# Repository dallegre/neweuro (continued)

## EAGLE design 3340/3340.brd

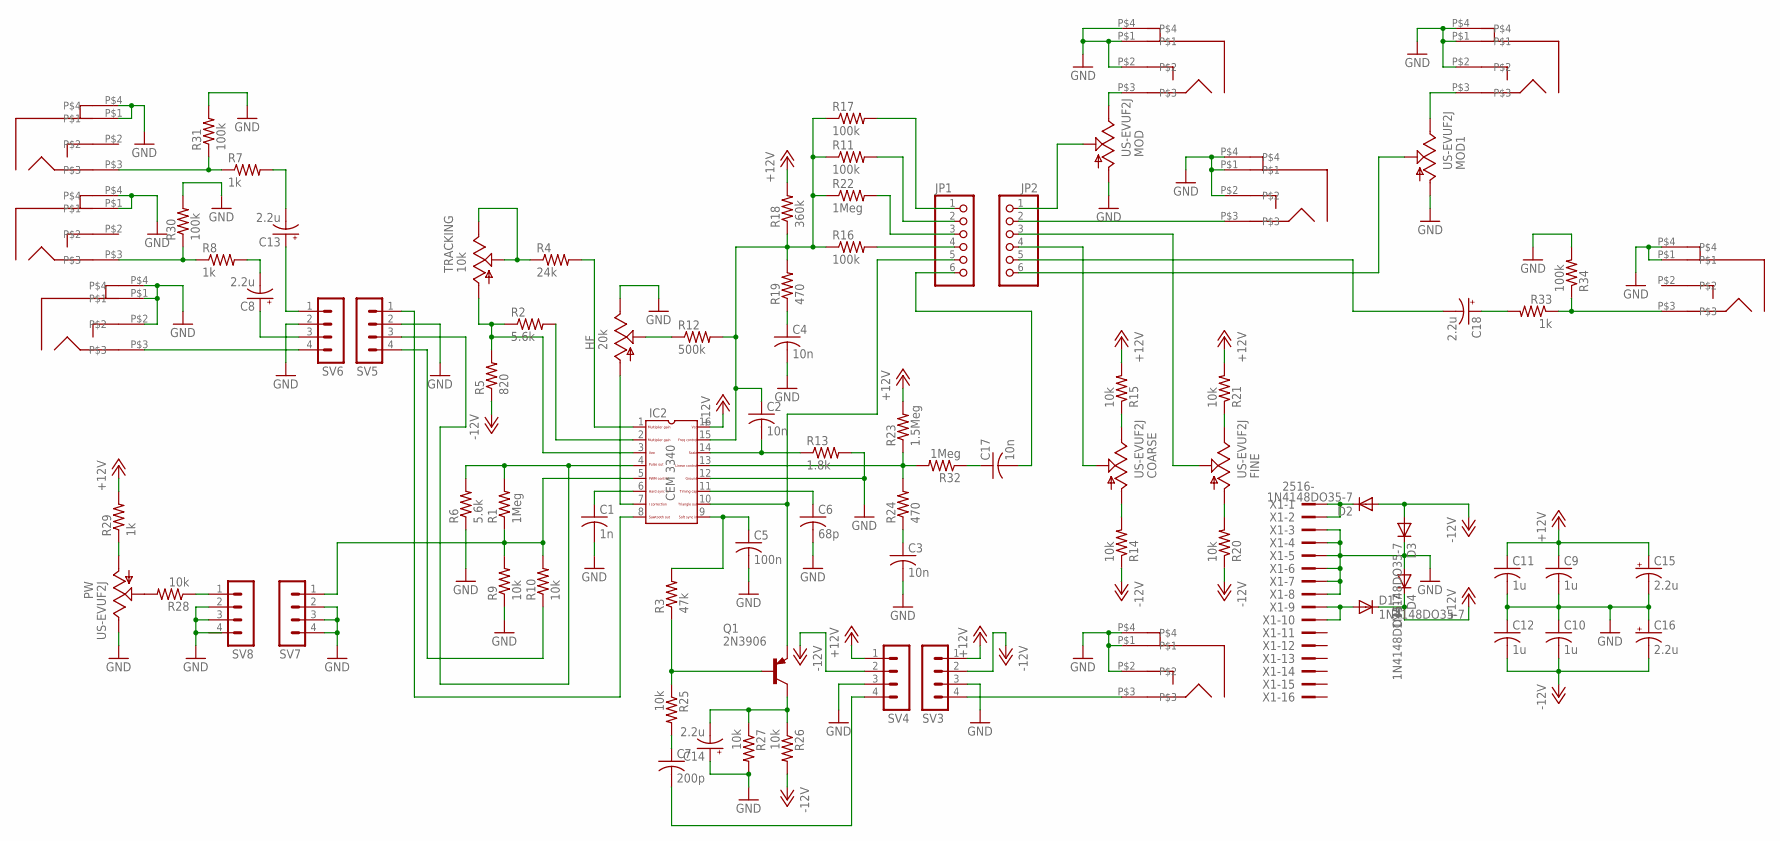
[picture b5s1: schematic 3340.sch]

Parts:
C1: 1n; C050-025X075
C2, C3, C4, C17: 10n; C050-025X075
C5: 100n; C050-025X075
C6: 68p; C050-025X075
C7: 200p; C050-025X075
C8, C13, C14, C15, C16, C18: 2.2u; E2,5-6
C9, C10, C11, C12: 1u; C050-025X075
COARSE: US-EVUF2J; EVUFXJ
CVIN1, CVIN2: PJ301BM
D1, D2, D3, D4: 1N4148DO35-7; DO35-7
EXPMOD: PJ301BM
FINE: US-EVUF2J; EVUFXJ
HF: 20k; S64W
IC2: CEM3340; DIL16
JP1, JP2: PINHD-1X6; 1X06
MOD, MOD1: US-EVUF2J; EVUFXJ
PULSE: PJ301BM
PW: US-EVUF2J; EVUFXJ
PWM: PJ301BM
Q1: 2N3906; TO92
R1, R22, R32: 1Meg; 0207/2V
R2, R6: 5.6k; 0207/2V
R3: 47k; 0207/2V
R4: 24k; 0207/2V
R5: 820; 0207/2V
R7, R8, R29, R33: 1k; 0207/7
R9, R10, R25, R26, R27: 10k; 0207/2V
R11, R16, R17: 100k; 0207/2V
R12: 500k; 0207/2V
R13: 1.8k; 0207/2V
R14, R15, R20, R21, R28: 10k; 0207/7
R18: 360k; 0207/2V
R19, R24: 470; 0207/2V
R23: 1.5Meg; 0207/2V
R30, R31, R34: 100k; 0207/7
SAW, SAW1: PJ301BM
SV3, SV4, SV5, SV6, SV7, SV8: MA04-1
SYNC: PJ301BM
TRACKING: 10k; S64W
X1: 2516-; PAK100/2500-16

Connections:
+12V: C9.1, C11.1, C15.+, D1.C, D4.C, IC2.16, R15.2, R18.2, R21.2, R23.2, R29.2, SV3.1, SV4.1
-12V: C10.2, C12.2, C16.-, D2.A, D3.A, R5.1, R14.1, R20.1, R26.2, SV3.2, SV4.2
GND: C1.2, C3.2, C4.2, C5.2, C6.2, C9.2, C10.1, C11.2, C12.1, C14.+, C15.-, C16.+, CVIN1.P$1, CVIN1.P$2, CVIN1.P$4, CVIN2.P$1, CVIN2.P$2, CVIN2.P$4, D3.C, D4.A, EXPMOD.P$1, EXPMOD.P$2, EXPMOD.P$4, HF.E, IC2.12, MOD.1 (A), MOD1.1 (A), PULSE.P$1, PULSE.P$4, PW.3 (E), PWM.P$1, PWM.P$2, PWM.P$4, R6.1, R9.1, R13.2, R27.2, R30.2, R31.2, R34.2, SAW.P$1, SAW.P$4, SAW1.P$1, SAW1.P$4, SV3.3, SV4.3, SV5.2, SV6.2, SV7.2, SV7.3, SV7.4, SV8.2, SV8.3, SYNC.P$1, SYNC.P$2, SYNC.P$4, X1.3, X1.4, X1.5, X1.6, X1.7, X1.8
unnamed: IC2.1, R4.2
unnamed: IC2.2, R2.2
unnamed: R4.1, TRACKING.E, TRACKING.S
unnamed: IC2.5, R1.1, R9.2, R10.2, SV7.1
unnamed: COARSE.2 (S), JP2.4
unnamed: COARSE.1 (A), R14.2
unnamed: COARSE.3 (E), R15.1
unnamed: IC2.4, R1.2, R6.2, SV5.3
unnamed: R10.1, SV5.4
unnamed: PWM.P$3, SV6.4
unnamed: C1.1, IC2.6
unnamed: IC2.8, SV5.1
unnamed: C13.-, R7.2
unnamed: R7.1, R31.1, SAW.P$3
unnamed: PULSE.P$3, R8.1, R30.1
unnamed: HF.A, IC2.7
unnamed: JP1.4, R16.2
unnamed: HF.S, R12.1
unnamed: C2.1, IC2.15, R11.1, R12.2, R16.1, R17.1, R18.1, R19.2, R22.1
unnamed: C5.1, IC2.9, R3.2
unnamed: JP1.1, R17.2
unnamed: EXPMOD.P$3, MOD.3 (E)
unnamed: C6.1, IC2.11
unnamed: C17.1, R32.1
unnamed: JP1.2, R11.2
unnamed: C13.+, SV6.1
unnamed: C8.+, SV6.3
unnamed: PW.2 (S), R28.2
unnamed: C2.2, IC2.14, R13.1
unnamed: SV3.4, SYNC.P$3
unnamed: JP2.1, MOD.2 (S)
unnamed: IC2.10, JP1.5, Q1.3 (E)
unnamed: FINE.1 (A), R20.2
unnamed: C4.1, R19.1
unnamed: CVIN1.P$3, JP2.2
unnamed: FINE.3 (E), R21.1
unnamed: FINE.2 (S), JP2.3
unnamed: IC2.13, R23.1, R24.2, R32.2
unnamed: JP1.3, R22.2
unnamed: C3.1, R24.1
unnamed: Q1.2 (B), R3.1, R25.1
unnamed: C7.1, R25.2
unnamed: D2.C, X1.1, X1.2
unnamed: C7.2, SV4.4
unnamed: D1.A, X1.9, X1.10
unnamed: C14.-, Q1.1 (C), R26.1, R27.1
unnamed: PW.1 (A), R29.1
unnamed: R28.1, SV8.1
unnamed: C8.-, R8.2
unnamed: IC2.3, R2.1, R5.2, TRACKING.A
unnamed: C17.2, JP1.6
unnamed: JP2.6, MOD1.2 (S)
unnamed: C18.+, R33.2
unnamed: R33.1, R34.1, SAW1.P$3
unnamed: C18.-, JP2.5
unnamed: CVIN2.P$3, MOD1.3 (E)

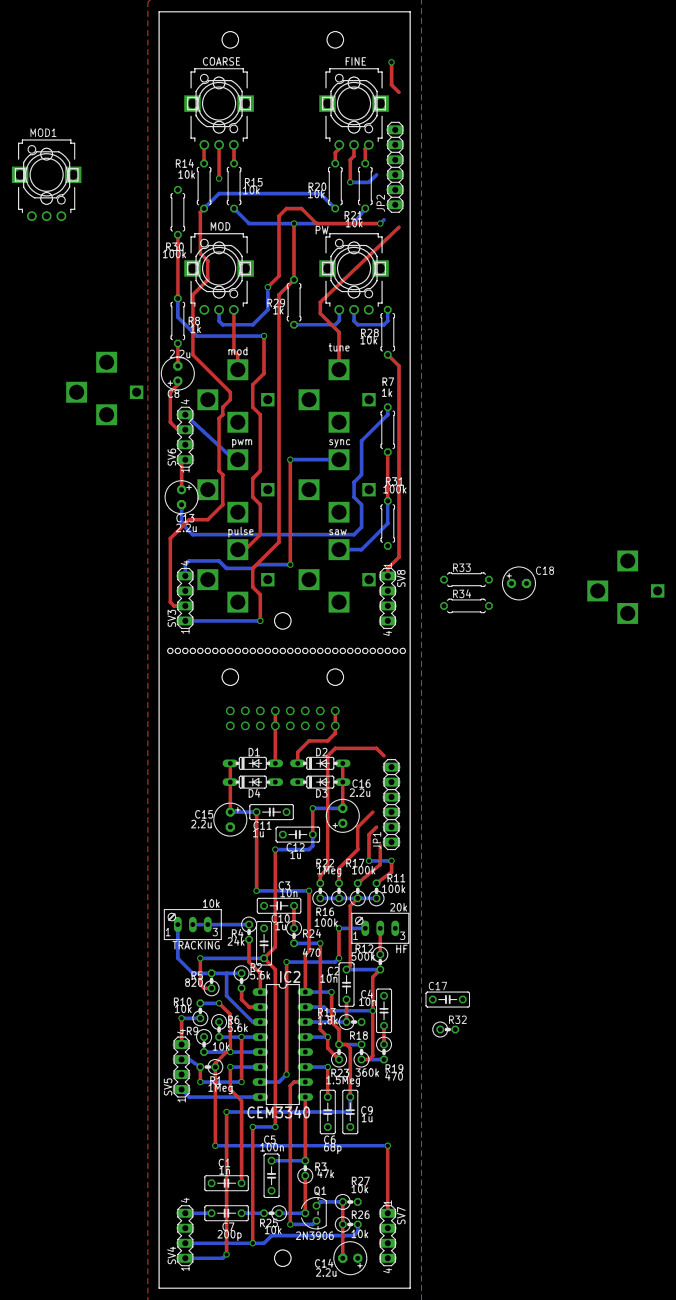
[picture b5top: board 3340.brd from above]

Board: 2 copper layers, 42.5 x 216.2 mm, 82 parts (1 on the bottom side), 59 nets.

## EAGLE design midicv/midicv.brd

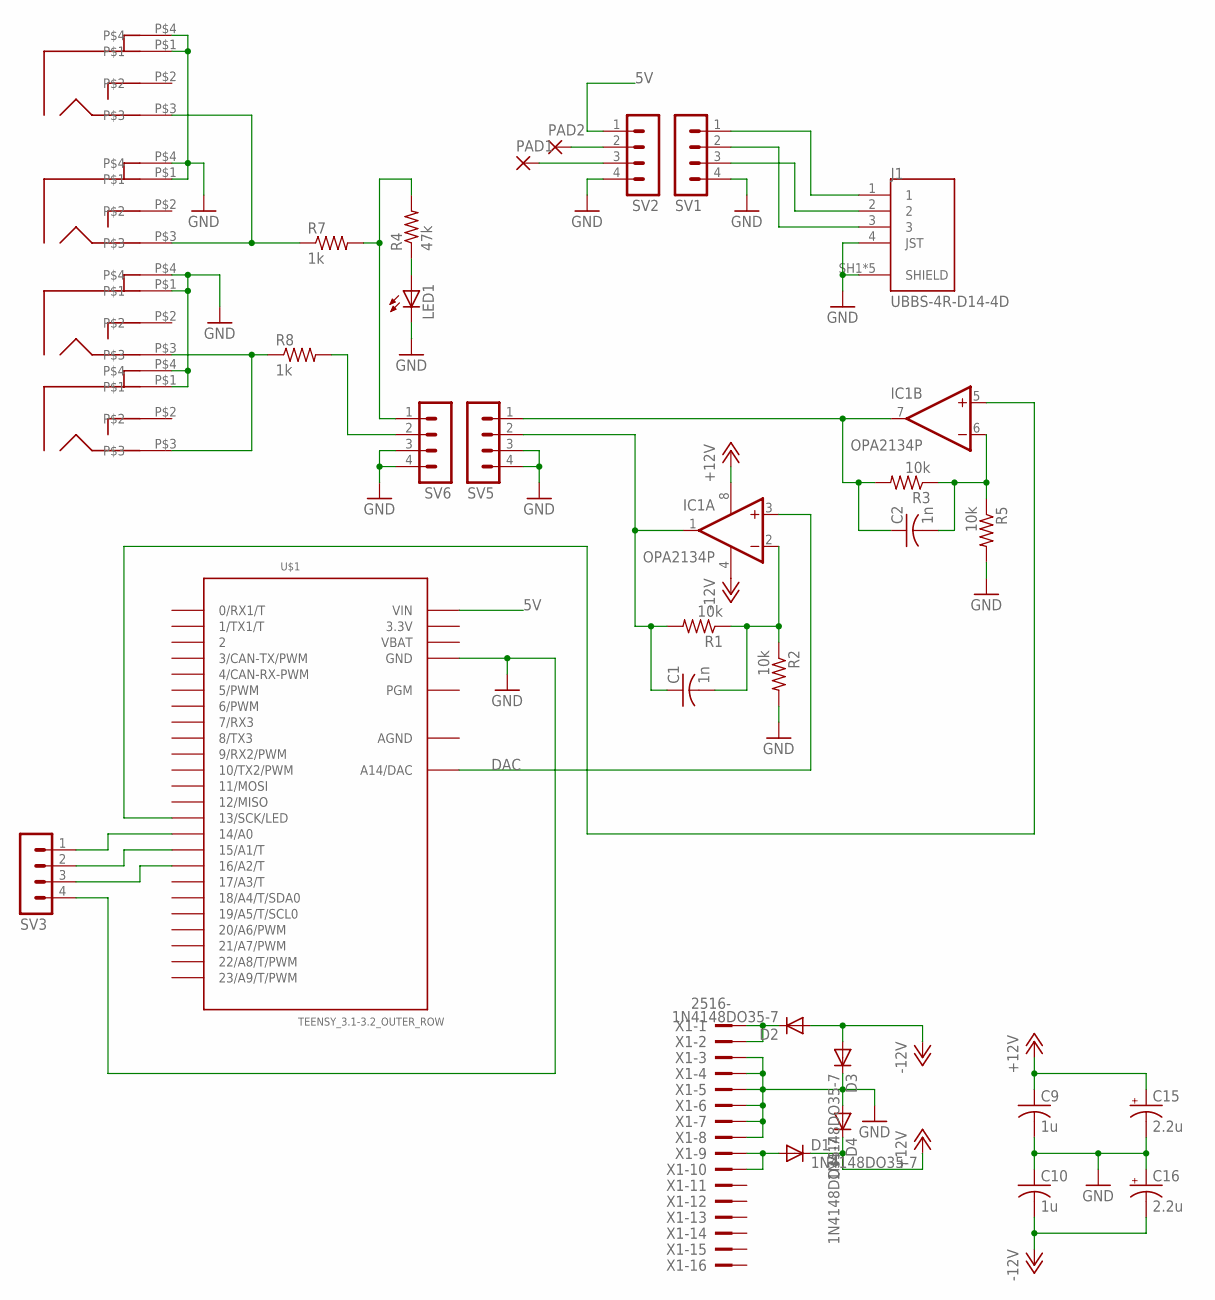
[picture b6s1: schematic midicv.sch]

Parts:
C1, C2: 1n; C050-025X075
C9, C10: 1u; C050-025X075
C15, C16: 2.2u; E2,5-6
CV, CV1: PJ301BM
D1, D2, D3, D4: 1N4148DO35-7; DO35-7
GATE, GATE1: PJ301BM
IC1: OPA2134P; DIL08
J1: UBBS-4R-D14-4D; JST_UBBS-4R-D14-4D
LED1: LED5MM
PAD1, PAD2: 2,0/0,9-R
R1, R2, R3, R5: 10k; 0207/2V
R4: 47k; 0207/7
R7, R8: 1k; 0207/7
SV1, SV2, SV3, SV5, SV6: MA04-1
U$1: TEENSY_3.1-3.2_OUTER_ROW; TEENSY_3.0-3.2&LC_OUTER_ROW
X1: 2516-; PAK100/2500-16

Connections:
3.3V: U$1.3.3V, U$1.3.3V1 (3.3V)
5V: SV2.1, U$1.VIN
+12V: C9.1, C15.+, D1.C, D4.C, IC1.8 (V+)
-12V: C10.2, C16.-, D2.A, D3.A, IC1.4 (V-)
AGND: U$1.AGND
DAC: IC1.3 (+IN), U$1.RESET/DAC (A14/DAC)
GND: C9.2, C10.1, C15.-, C16.+, CV.P$1, CV.P$4, CV1.P$1, CV1.P$4, D3.C, D4.A, GATE.P$1, GATE.P$4, GATE1.P$1, GATE1.P$4, J1.4 (JST), J1.SH1 (SHIELD), J1.SH2 (SHIELD), J1.SH3 (SHIELD), J1.SH4 (SHIELD), J1.SH5 (SHIELD), LED1.K (C), R2.2, R5.2, SV1.4, SV2.4, SV3.4, SV5.3, SV5.4, SV6.3, SV6.4, U$1.GND, U$1.GND1 (GND), X1.3, X1.4, X1.5, X1.6, X1.7, X1.8
unnamed: C1.1, IC1.1 (OUT), R1.2, SV5.2
unnamed: C2.1, IC1.7 (OUT), R3.2, SV5.1
unnamed: SV3.1, U$1.14/A0
unnamed: IC1.5 (+IN), U$1.13 (13/SCK/LED)
unnamed: C1.2, IC1.2 (-IN), R1.1, R2.1
unnamed: PAD2.1, SV2.2
unnamed: LED1.A, R4.1
unnamed: PAD1.1, SV2.3
unnamed: C2.2, IC1.6 (-IN), R3.1, R5.1
unnamed: J1.3, SV1.2
unnamed: J1.1, SV1.1
unnamed: SV3.2, U$1.15/A1 (15/A1/T)
unnamed: GATE.P$3, GATE1.P$3, R7.1
unnamed: CV.P$3, CV1.P$3, R8.1
unnamed: SV3.3, U$1.16/A2 (16/A2/T)
unnamed: J1.2, SV1.3
unnamed: R4.2, R7.2, SV6.1
unnamed: D2.C, X1.1, X1.2
unnamed: D1.A, X1.9, X1.10
unnamed: R8.2, SV6.2
VBAT: U$1.VBAT

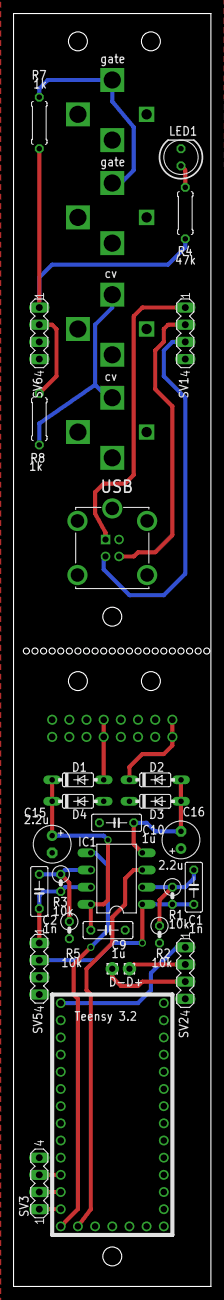
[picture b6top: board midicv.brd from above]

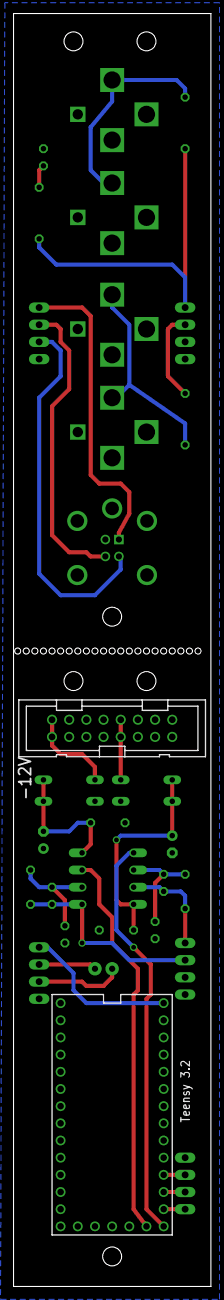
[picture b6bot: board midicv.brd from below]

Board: 2 copper layers, 29.2 x 188.3 mm, 33 parts (2 on the bottom side), 26 nets.

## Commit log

2019-12-14 added 3320 and 2045 and vcf3 filters 3340 osc
2019-12-14 removing extemporaneous files from vcf3
2019-12-14 fixed the header position in vcf3 and fixed the 2 pole polarity
2019-12-14 fixed the 2 pole polarity for 3320
2019-12-15 added usb to cv converter
2019-12-21 added center freq trimpot to vcf3, fixed v/oct tracking
2019-12-21 fixed footprints on top 3320 board
2019-12-21 added input atten pots to 3320 and re arranged front
2019-12-21 fixed the levels for the 3340 and vcf3
2019-12-23 sent out vcf3 and 3320 for re spin
2019-12-30 added state variable filter, changed pw resistor on vco
2019-12-30 added bom for 3340 vco
2020-01-23 started making a board for the state variable filter
2020-01-26 finished the rough draft of the state variable board
2020-01-26 fixed placement of knobs and jacks on svf
2020-01-30 made post fab component changes to 3320 and some fixes to svf board
2020-02-05 sent svf to fab. fixed some significatn errors
2020-02-08 fixed usb polatiry on midicv. moved holes
2020-02-09 added panel for 3320 and updated panel for vcf3
2020-02-10 added front panel for svf, updated panels for ladder and 3320
2020-02-10 updated panels. Ordered the 3320 panel.
2020-02-15 updated svf panel to account for errors on the board
2020-02-22 respun the svf. changed a few components on the 3320
2020-02-29 fixed svf panel
2020-04-02 adding digital cv source to repo
2020-04-02 cleaned up cvsource board, flipped power connector
2020-04-03 added usb and moved things on cvsource
2020-04-04 moved things around on cvsource
2020-04-11 more work on cvsource and added zipped code
2020-04-14 added tri and linear mod to vco, fixed serious errors with cvsource
2020-04-14 ordered cvsource
2020-05-02 got the cv source back from board fab. added panel.
2020-05-30 updated the cvsource fw
2020-12-09 upated the 2045 filter
2021-08-09 updated svf with dc offset trim pots and transistors for biasing
